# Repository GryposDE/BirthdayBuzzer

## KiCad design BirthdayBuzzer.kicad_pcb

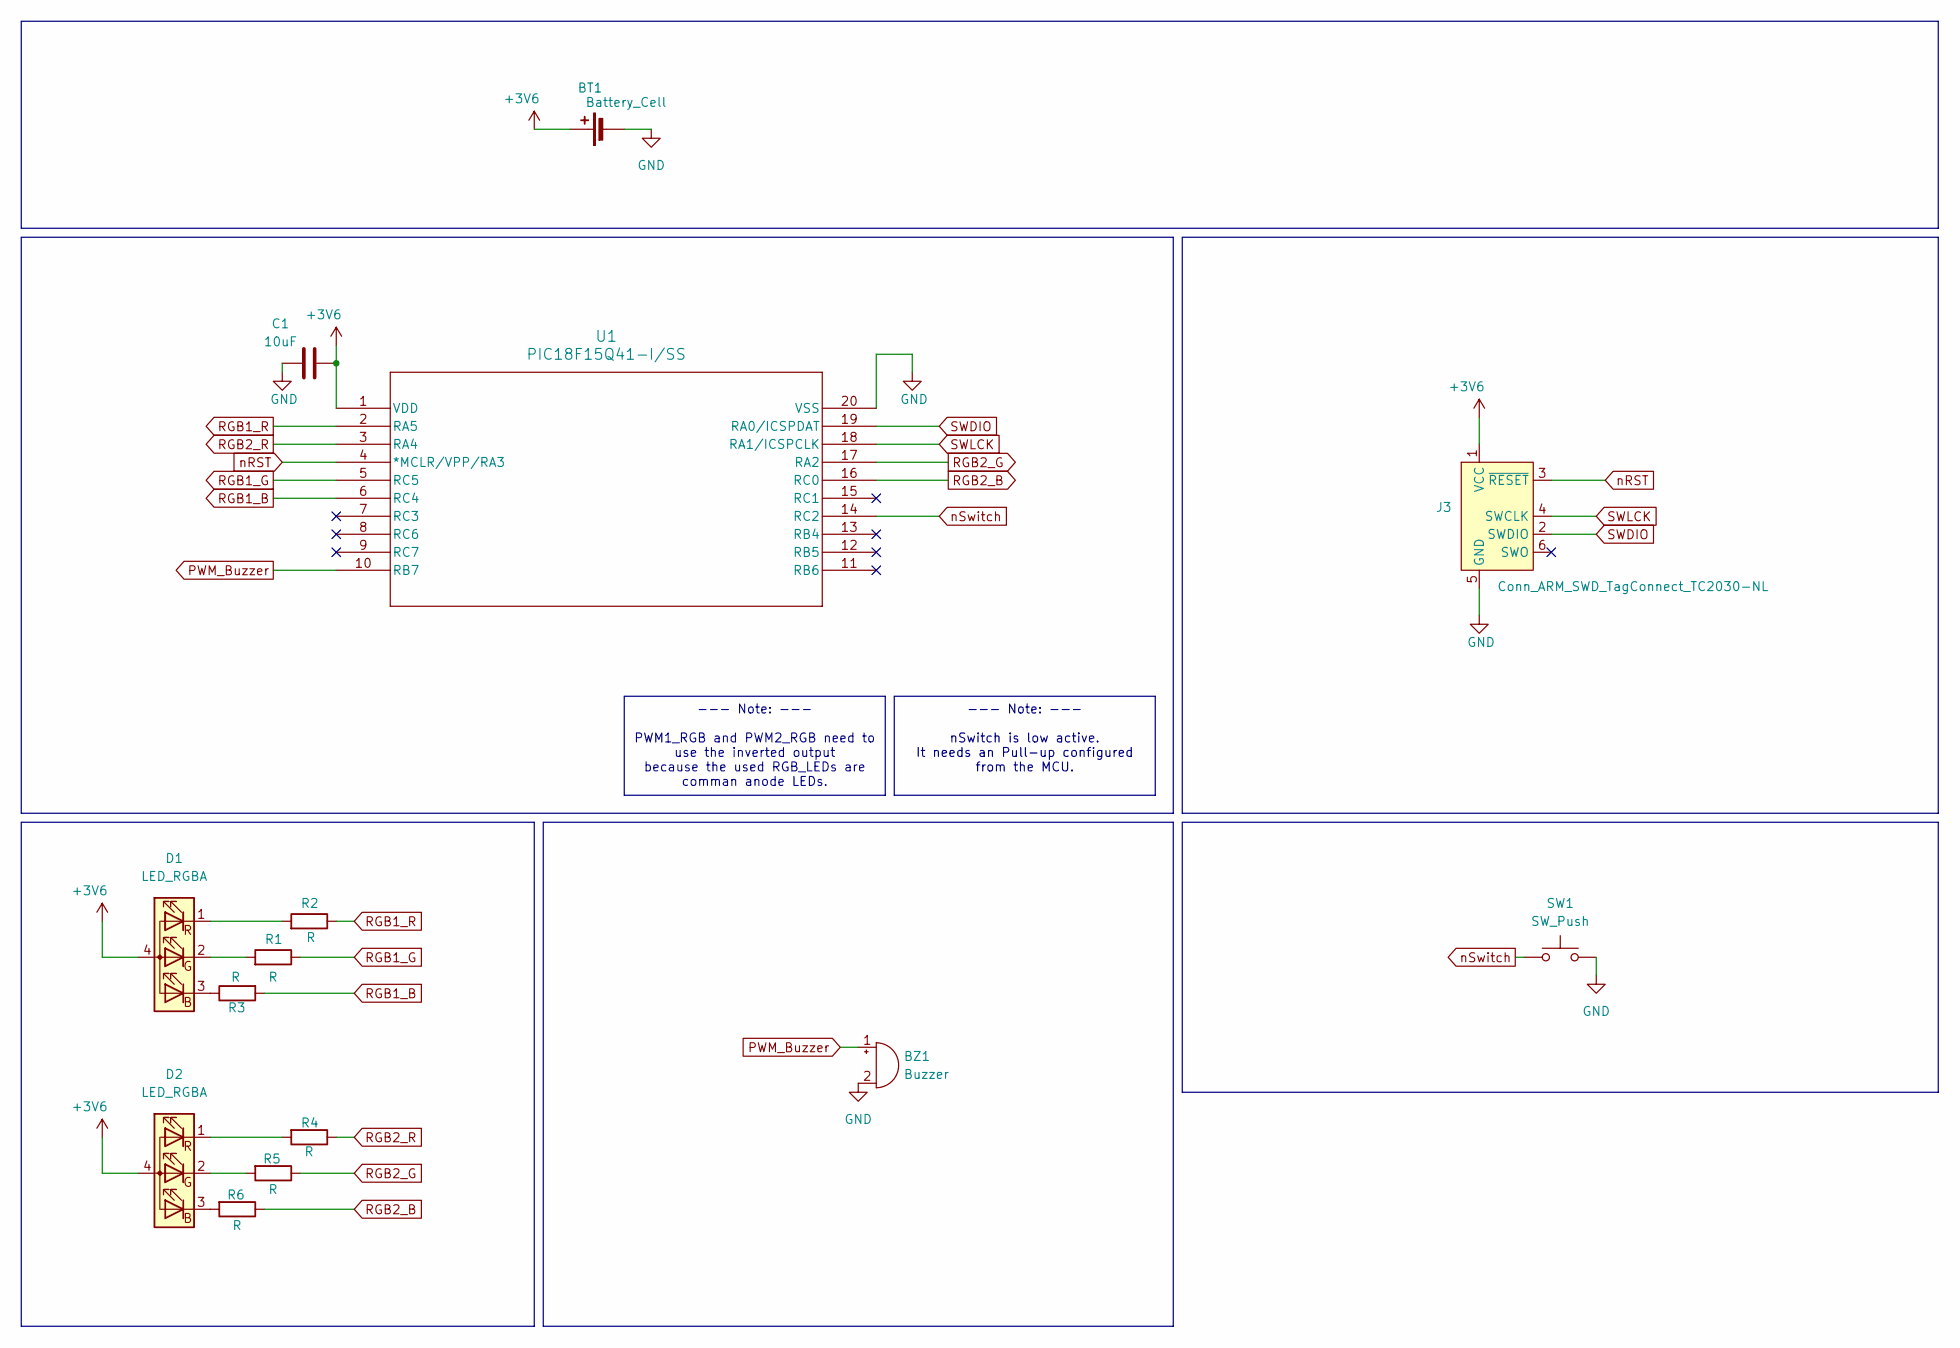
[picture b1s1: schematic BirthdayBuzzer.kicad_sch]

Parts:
BT1: Battery_Cell; BatteryHolder_Keystone_3034_1x20mm
BZ1: Buzzer; MagneticBuzzer_ProSignal_ABI-009-RC
C1: 10uF; C_Disc_D4.3mm_W1.9mm_P5.00mm
D1, D2: LED_RGBA; cr_RGB_LED
J3: Conn_ARM_SWD_TagConnect_TC2030-NL; Tag-Connect_TC2030-IDC-NL_2x03_P1.27mm_Vertical
R1, R2, R3, R4, R5, R6: R; R_Axial_DIN0207_L6.3mm_D2.5mm_P7.62mm_Horizontal
SW1: SW_Push; SW_SPST_PTS647_Sx38
U1: PIC18F15Q41-I/SS; SSOP20_SS_MCH

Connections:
+3V6: BT1.1 (+), C1.2, D1.4 (A), D2.4 (A), J3.1 (VCC), U1.1 (VDD)
GND: BT1.2 (-), BZ1.2 (-), C1.1, J3.5 (GND), SW1.2, U1.20 (VSS)
unnamed: D1.3 (BK), R3.1
unnamed: D1.2 (GK), R1.2
unnamed: D1.1 (RK), R2.2
unnamed: D2.3 (BK), R6.2
unnamed: D2.2 (GK), R5.2
unnamed: D2.1 (RK), R4.2
PWM_Buzzer: BZ1.1 (+), U1.10 (RB7)
RGB1_B: R3.2, U1.6 (RC4)
RGB1_G: R1.1, U1.5 (RC5)
RGB1_R: R2.1, U1.2 (RA5)
RGB2_B: R6.1, U1.16 (RC0)
RGB2_G: R5.1, U1.17 (RA2)
RGB2_R: R4.1, U1.3 (RA4)
SWDIO: J3.2 (SWDIO), U1.19 (RA0/ICSPDAT)
SWLCK: J3.4 (SWCLK), U1.18 (RA1/ICSPCLK)
nRST: J3.3 (~RESET), U1.4 (*MCLR/VPP/RA3)
nSwitch: SW1.1, U1.14 (RC2)

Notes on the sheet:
--- Note: --- PWM1_RGB and PWM2_RGB need to use the inverted output because the used RGB_LEDs are comman anode LEDs.
--- Note: --- nSwitch is low active. It needs an Pull-up configured from the MCU.

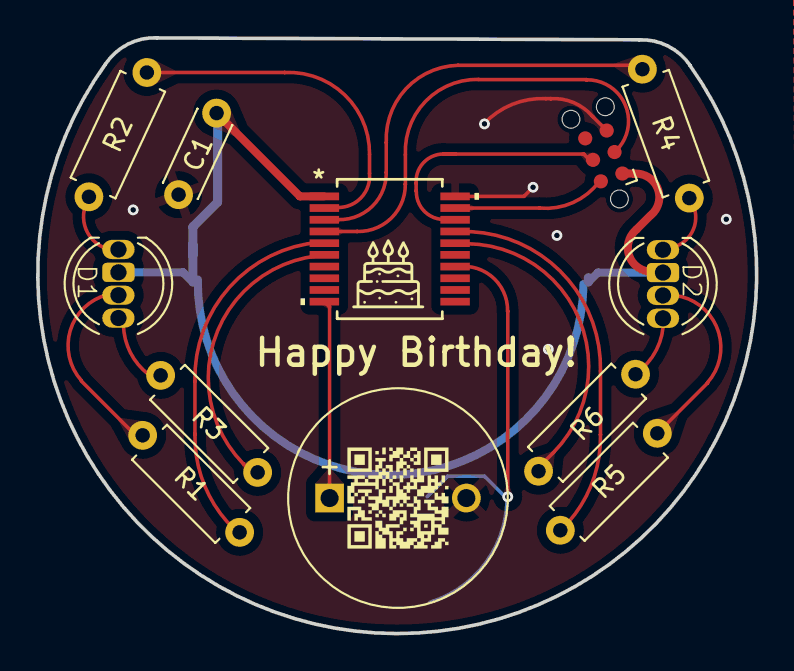
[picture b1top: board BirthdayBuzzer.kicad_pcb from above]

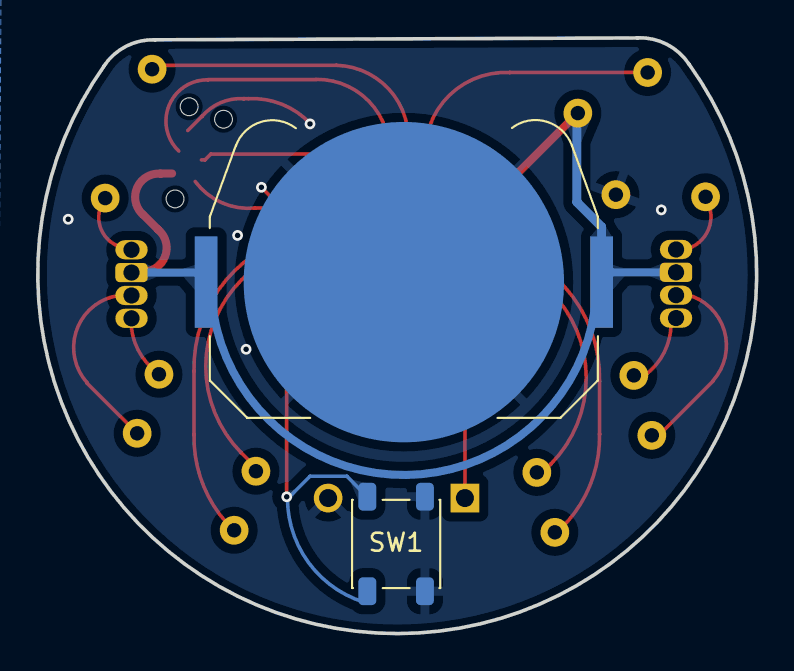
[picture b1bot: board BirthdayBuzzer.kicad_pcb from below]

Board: 2 copper layers, 39.9 x 33.1 mm, 14 parts (2 on the bottom side), 19 nets.

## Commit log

2025-04-12 BirthdayBuzzer_v1.0
2025-04-13 Added Github QR-Code to desgin
2025-04-13 Added gitignore
2025-04-13 Cleaned up schematics and added notes
2025-04-18 Fixed Capacitor in Schematics and GND in layout
